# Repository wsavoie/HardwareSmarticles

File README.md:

# HardwareSmarticles
Contains all the relevant files for the hardware version of the smarticle as of 8/3/15

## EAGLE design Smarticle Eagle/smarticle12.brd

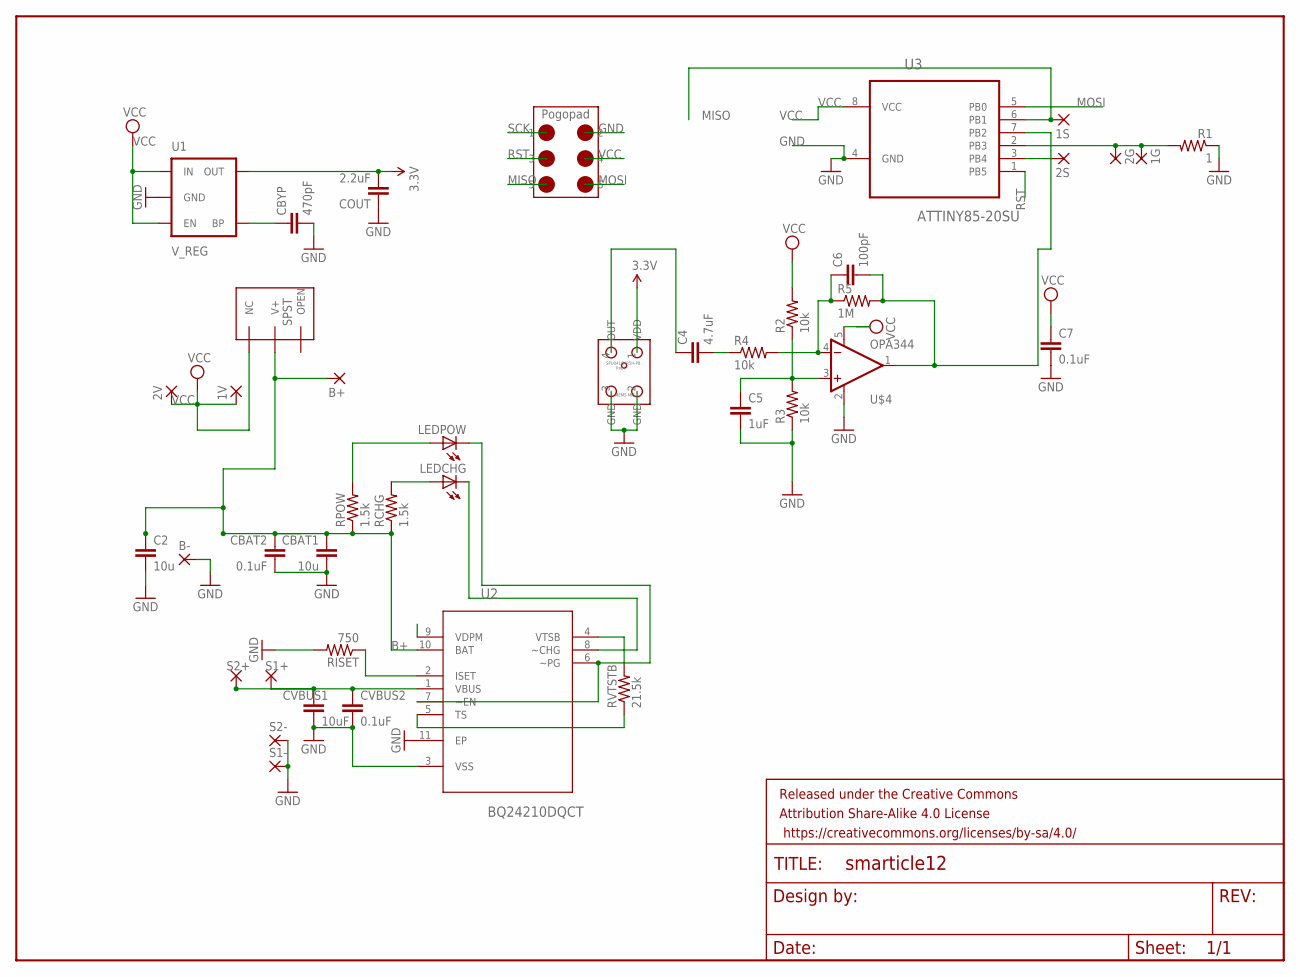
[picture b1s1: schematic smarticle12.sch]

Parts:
1G, 1S, 1V, 2G, 2S, 2V: 1,6/0,8
B+: 1,6/0,8
B-: 1,6/0,8
C2: 10u; 0603-CAP
C4: 4.7uF; 0603-CAP
C5: 1uF; 0603-CAP
C6: 100pF; 0603-CAP
C7: 0.1uF; 0603-CAP
CBAT1: 10u; 0805
CBAT2: 0.1uF; 0603-CAP
CBYP: 470pF; 0603-CAP
COUT: 2.2uF; 0603-CAP
CVBUS1: 10uF; 1206
CVBUS2: 0.1uF; 0603-CAP
FRAME1: FRAME-LETTERNO_PACKAGE; DUMMY
LEDCHG: LEDCHIPLED_0603; CHIPLED_0603
LEDPOW: LEDCHIPLED_0603; CHIPLED_0603
R1: 1; 0805
R2, R3, R4: 10k; 0603-RES
R5: 1M; 0603-RES
RCHG: 1.5k; 0603-RES
RISET: 750; 0603-RES
RPOW: 1.5k; 0603-RES
RVTSTB: 21.5k; 0603-RES
S1+, S1-, S2+, S2-: 1,6/0,8
U1: V_REG; SOT23-5
U2: BQ24210DQCT; SON50P200X300X80-11N
U3: ATTINY85-20SU; SOIC127P798X216-8N
U$1: 2X3POGOPADS; 3X2POGOPADS
U$2: WILL_SWITCH; WILL-SWITCH
U$3: MEMSMICRO; MEMSMIC
U$4: OPA344; SOT23-5

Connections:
3.3V: COUT.2, U1.5 (OUT), U$3.1 (VDD)
B+: B+.1, C2.1, CBAT1.1, CBAT2.1, RCHG.1, RPOW.1, U2.10 (BAT), U$2.V+
GND: B-.1, C2.2, C5.2, C7.2, CBAT1.2, CBAT2.2, CBYP.2, COUT.1, CVBUS1.2, CVBUS2.2, R1.1, R3.1, RISET.2, S1-.1, S2-.1, U1.2 (GND), U2.3 (VSS), U2.11 (EP), U3.4 (GND), U$1.2, U$3.2 (GND), U$3.3 (GND), U$4.2 (V-)
MISO: 1S.1, U3.6 (PB1), U$1.5
MOSI: U3.5 (PB0), U$1.6
unnamed: 2S.1, U3.3 (PB4)
unnamed: LEDPOW.A, RPOW.2
unnamed: LEDCHG.A, RCHG.2
unnamed: CBYP.1, U1.4 (BP)
unnamed: RVTSTB.1, U2.5 (TS)
unnamed: RVTSTB.2, U2.4 (VTSB)
unnamed: 1G.1, 2G.1, R1.2, U3.2 (PB3)
unnamed: CVBUS1.1, CVBUS2.1, S1+.1, S2+.1, U2.1 (VBUS)
unnamed: LEDPOW.C, U2.6 (~PG), U2.7 (~EN)
unnamed: RISET.1, U2.2 (ISET)
unnamed: C4.1, U$3.4 (OUT)
unnamed: LEDCHG.C, U2.8 (~CHG)
unnamed: C4.2, R4.1
unnamed: C5.1, R2.1, R3.2, U$4.3 (+IN)
unnamed: C6.1, R4.2, R5.1, U$4.4 (-IN)
RST: U3.1 (PB5), U$1.3
SCK: C6.2, R5.2, U3.7 (PB2), U$1.1, U$4.1 (OUT)
VCC: 1V.1, 2V.1, C7.1, R2.2, U1.1 (IN), U1.3 (EN), U3.8 (VCC), U$1.4, U$2.NC, U$4.5 (V+)

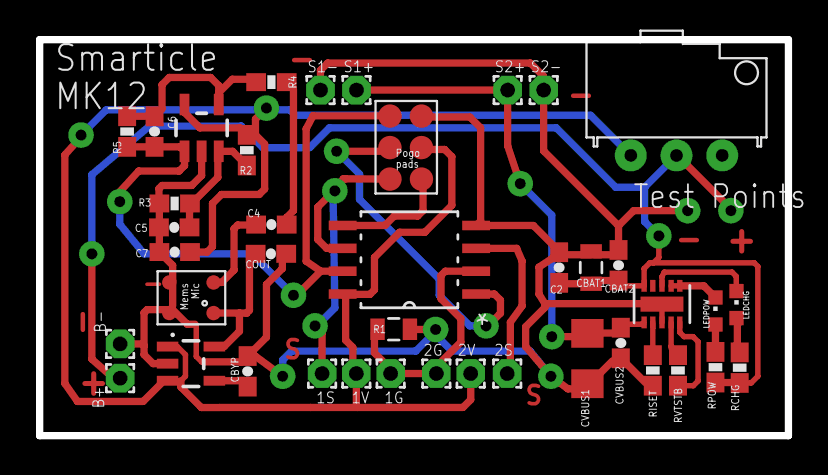
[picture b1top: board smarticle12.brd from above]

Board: 2 copper layers, 41.6 x 22.0 mm, 42 parts (0 on the bottom side), 23 nets.

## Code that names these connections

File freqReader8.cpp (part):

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//https://github.com/kehribar/proper-tiny-arduino/blob/master/pta/analog.c
// ATtiny45/85 Pin map
//                        +-\/-+
// Reset/Ain0 (D 5) PB5  1|o   |8  Vcc
//       Ain3 (D 3) PB3  2|    |7  PB2 (D 2) Ain1 7
//       Ain2 (D 4) PB4  3|    |6  PB1 (D 1) pwm1
//                  GND  4|    |5  PB0 (D 0) pwm0 <-- connect LED here
//                        +----+
uint8_t matchCount = 0;
uint16_t prevVal = 0;
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  
//attiny datasheet 17.13.1 p134
//when using analog pins you must use pin value not port
uint8_t LED   = PB3;//0;//0;
uint8_t SP2   = PB1;//1;//1;
uint8_t mic   = 1;//A1;//int mic = A1;P2 //electret //or 7
uint8_t currP = 3;//3;//int currP = A3;P3
uint8_t SP1   = PB4;//4; //4;
uint16_t oldTime;

  Servo8Bit S1;  //create a servo object.
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
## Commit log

2015-08-03 code smarticle's attiny85 to perform different frequency activated gaits
2015-08-03 added smarticle eagle files
2015-08-03 added solidworks files
2015-11-16 edited at some point?
2016-01-07 added rectified square gait, changed delay amount, and maximum and minimum values for the movement size
2016-09-12 added git ignore file to not add elf, hex,lst,map and o files
2016-09-12 removed files I was ignore in git ignore

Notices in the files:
parts and their libraries:
SparkFun-Aesthetics: Licensing: Creative Commons ShareAlike 4.0 International - https://creativecommons.org/licenses/by-sa/4.0
SparkFun-Aesthetics: Released under the Creative Commons Attribution Share-Alike 4.0 License
SparkFun-Aesthetics: https://creativecommons.org/licenses/by-sa/4.0
